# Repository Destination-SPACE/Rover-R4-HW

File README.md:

# Destination Automation R4 - Hardware test
Hardware repository for the Destination Automation R4 robotic rover platform

## Features
- Seeeduino XIAO SAMD21 M0 microcontroller
- +5V & +8V voltage regulators
- 128x64 OLED display
- 2x DRV8871 full bridge motor drivers
- Line follwer connector (JST-PH)
- 2x input buttons

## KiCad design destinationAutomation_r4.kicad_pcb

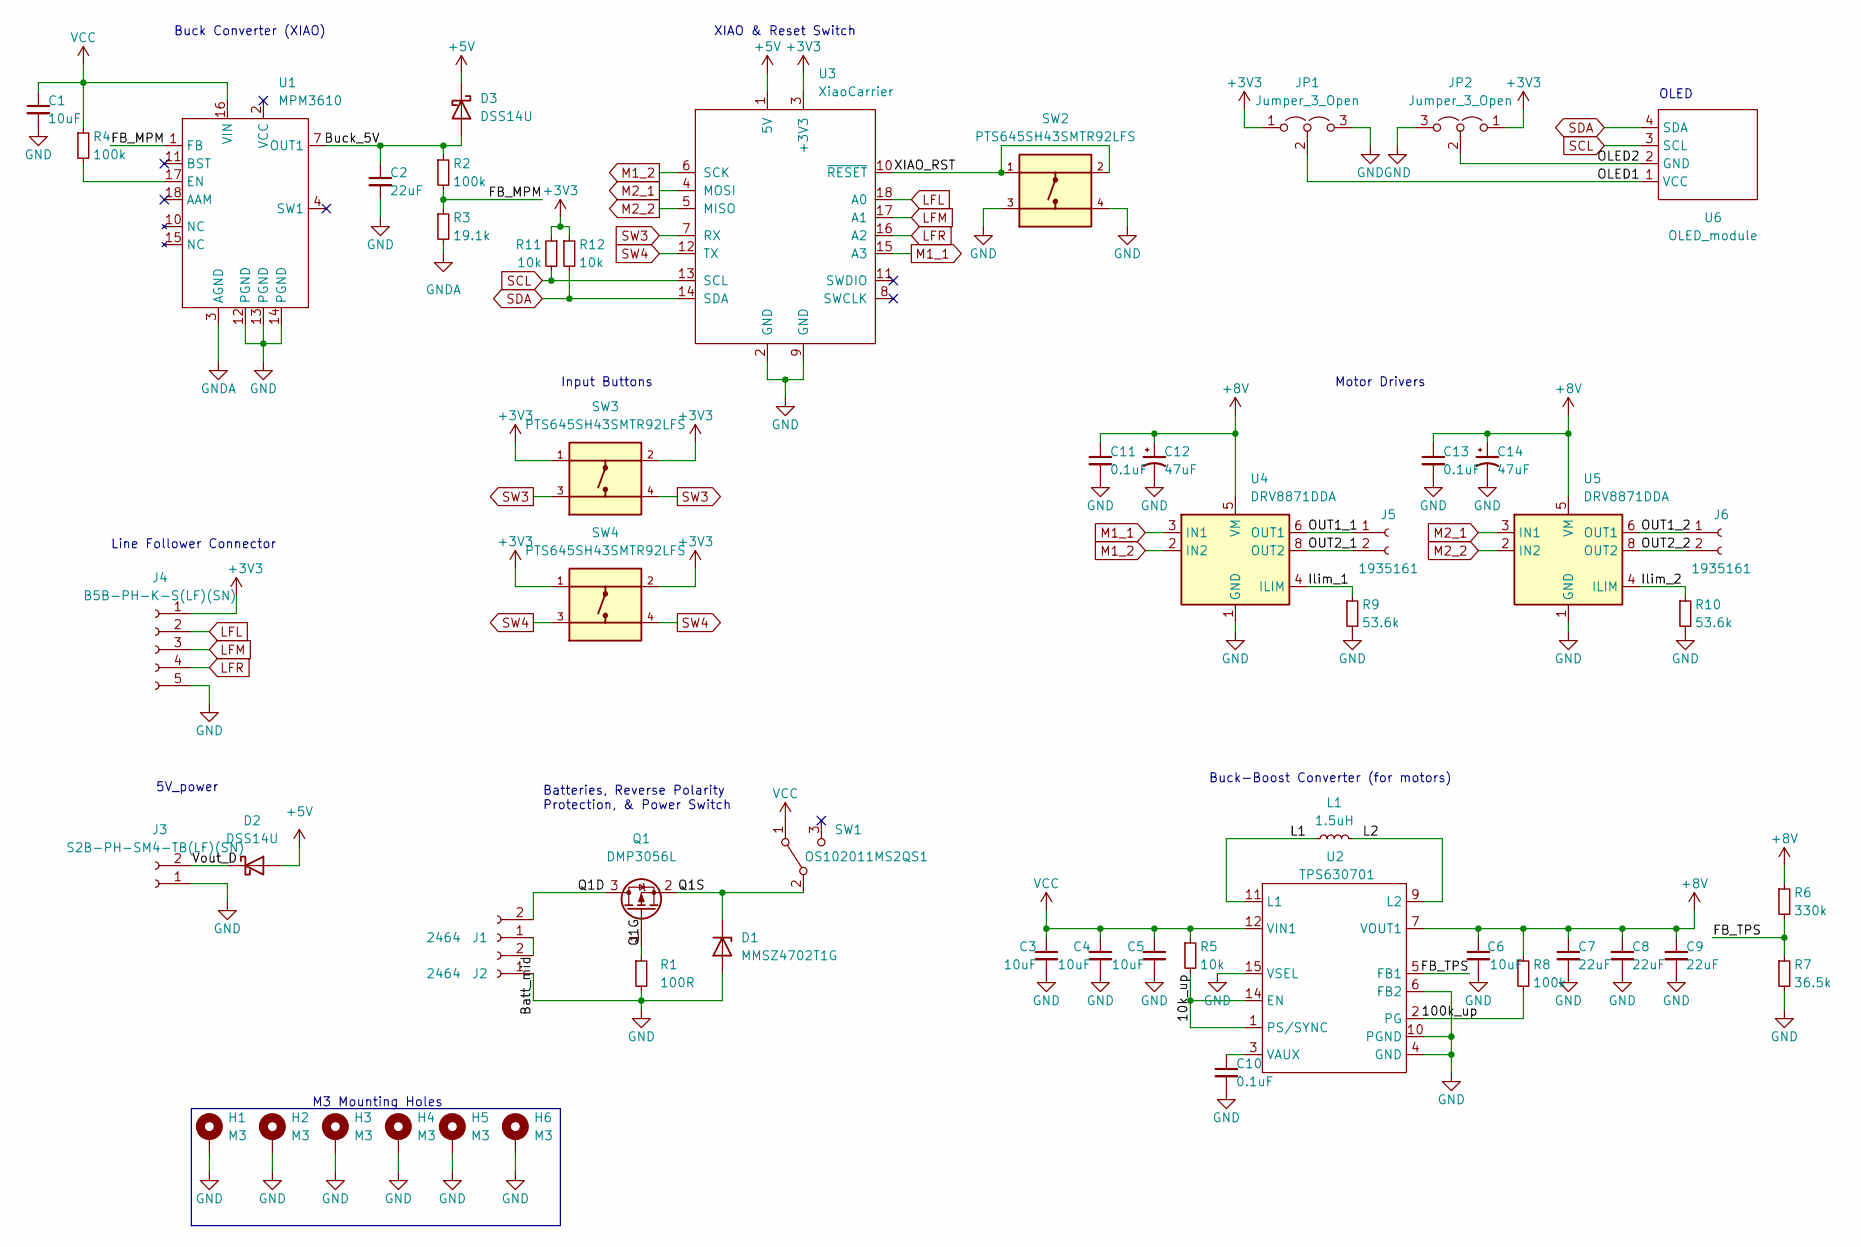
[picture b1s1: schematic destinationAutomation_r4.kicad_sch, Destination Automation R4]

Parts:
C1, C3, C4: 10uF; C_0805_2012Metric; mpn C2012X7R1A106K125AC
C2, C7, C8, C9: 22uF; C_0805_2012Metric; mpn C2012X5R1C226M125AC
C5, C6: 10uF; C_0603_1608Metric; mpn C1608X5R1C106M080AB
C10, C11, C13: 0.1uF; C_0603_1608Metric; mpn CGA3E2X7R1E104K080AA
C12, C14: 47uF; CP_Elec_6.3x7.7; mpn EDK476M035A9GAA
D1: MMSZ4702T1G; D_SOD-123; mpn MMSZ4702T1G
D2, D3: DSS14U; D_SOD-123F; mpn DSS14U
H1, H2, H3, H4, H5, H6: M3; MountingHole_3.2mm_M3_DIN965_Pad
J1, J2: 2464; 2464BatteryPack; mpn 2464
J3: S2B-PH-SM4-TB(LF)(SN); JST_PH_S2B-PH-SM4-TB_1x02-1MP_P2.00mm_Horizontal; mpn S2B-PH-SM4-TB(LF)(SN)
J4: B5B-PH-K-S(LF)(SN); JST_PH_B5B-PH-K_1x05_P2.00mm_Vertical; mpn B5B-PH-K-S(LF)(SN)
J5, J6: 1935161; SolderWire-1sqmm_1x02_P5.4mm_D1.4mm_OD2.7mm; mpn 1935161
JP1, JP2: Jumper_3_Open; SolderJumper-3_P1.3mm_Open_RoundedPad1.0x1.5mm
L1: 1.5uH; DRA74; mpn DR74-1R5-R
Q1: DMP3056L; SOT-23; mpn DMP3056L-7
R1: 100R; R_0603_1608Metric; mpn CRCW0603100RFKEA
R2, R4, R8: 100k; R_0603_1608Metric; mpn CRCW0603100KJNEA
R3: 19.1k; R_0603_1608Metric; mpn CRCW060319K1FKEA
R5, R11, R12: 10k; R_0603_1608Metric; mpn CRCW060310K0JNEB
R6: 330k; R_0603_1608Metric; mpn CRCW0603330KFKEAC
R7: 36.5k; R_0603_1608Metric; mpn CRCW060336K5FKEA
R9, R10: 53.6k; R_0603_1608Metric; mpn CRCW060353K6FKEAC
SW1: OS102011MS2QS1; SW_SPDT; mpn OS102011MS2QS1
SW2, SW3, SW4: PTS645SH43SMTR92LFS; MF_Switches-TACT6MM; mpn PTS645SH43SMTR92LFS
U1: MPM3610; mpn MPM3610GQV-P
U2: TPS630701; RNM0015A; mpn TPS63070RNMR
U3: XiaoCarrier; mpn 102010328
U4: DRV8871DDA; Texas_HTSOP-8-1EP_3.9x4.9mm_P1.27mm_EP2.95x4.9mm_Mask2.4x3.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; mpn DRV8871DDAR
U5: DRV8871DDA; Texas_HTSOP-8-1EP_3.9x4.9mm_P1.27mm_EP2.95x4.9mm_Mask2.4x3.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; mpn DRV8871DDA
U6: OLED_module

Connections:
+3V3: J4.1, JP1.1 (A), JP2.1 (A), R11.1, R12.1, SW3.1, SW3.2, SW4.1, SW4.2, U3.3 (+3V3)
+5V: D2.2 (A), D3.1 (K), U3.1 (5V)
+8V: C6.1, C7.1, C8.1, C9.1, C11.1, C12.1, C13.1, C14.1, R6.1, R8.1, U2.7 (VOUT1), U4.5 (VM), U5.5 (VM)
/10k_up: R5.2, U2.1 (PS/SYNC), U2.14 (EN)
/100k_up: R8.2, U2.2 (PG)
/Batt_mid: J1.1, J2.2
/Buck_5V: C2.1, D3.2 (A), R2.1, U1.7 (OUT1)
/FB_MPM: R2.2, R3.1, U1.1 (FB)
/FB_TPS: R6.2, R7.1, U2.5 (FB1)
/Ilim_1: R9.1, U4.4 (ILIM)
/Ilim_2: R10.1, U5.4 (ILIM)
/L1: L1.1, U2.11 (L1)
/L2: L1.2, U2.9 (L2)
/OLED1: JP1.2 (C), U6.1 (VCC)
/OLED2: JP2.2 (C), U6.2 (GND)
/OUT1_1: J5.1, U4.6 (OUT1)
/OUT1_2: J6.1, U5.6 (OUT1)
/OUT2_1: J5.2, U4.8 (OUT2)
/OUT2_2: J6.2, U5.8 (OUT2)
/Q1D: J1.2, Q1.3 (D)
/Q1G: Q1.1 (G), R1.1
/Q1S: D1.1 (K), Q1.2 (S), SW1.2 (B)
/Vout_D: D2.1 (K), J3.2
/XIAO_RST: SW2.1, SW2.2, U3.10 (~RESET)
GND: C1.2, C2.2, C3.2, C4.2, C5.2, C6.2, C7.2, C8.2, C9.2, C10.2, C11.2, C12.2, C13.2, C14.2, D1.2 (A), H1.1, H2.1, H3.1, H4.1, H5.1, H6.1, J2.1, J3.1, J4.5, JP1.3 (B), JP2.3 (B), R1.2, R7.2, R9.2, R10.2, SW2.3, SW2.4, U1.12 (PGND), U1.13 (PGND), U1.14 (PGND), U2.4 (GND), U2.6 (FB2), U2.10 (PGND), U2.15 (VSEL), U3.2 (GND), U3.9 (GND), U4.1 (GND), U4.7 (GND), U4.9 (GND), U5.1 (GND), U5.7 (GND), U5.9 (GND)
GNDA: R3.2, U1.3 (AGND)
LFL: J4.2, U3.18 (A0)
LFM: J4.3, U3.17 (A1)
LFR: J4.4, U3.16 (A2)
M1_1: U3.15 (A3), U4.3 (IN1)
M1_2: U3.6 (SCK), U4.2 (IN2)
M2_1: U3.4 (MOSI), U5.3 (IN1)
M2_2: U3.5 (MISO), U5.2 (IN2)
unnamed: C10.1, U2.3 (VAUX)
unnamed: R4.2, U1.17 (EN)
SCL: R11.2, U3.13 (SCL), U6.3 (SCL)
SDA: R12.2, U3.14 (SDA), U6.4 (SDA)
SW3: SW3.3, SW3.4, U3.7 (RX)
SW4: SW4.3, SW4.4, U3.12 (TX)
VCC: C1.1, C3.1, C4.1, C5.1, R4.1, R5.1, SW1.1 (A), U1.16 (VIN), U2.12 (VIN1)

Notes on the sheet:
Buck-Boost Converter (for motors)
Input Buttons
XIAO & Reset Switch
Buck Converter (XIAO)
5V_power
M3 Mounting Holes
Line Follower Connector
OLED
Motor Drivers
Batteries, Reverse Polarity Protection, & Power Switch

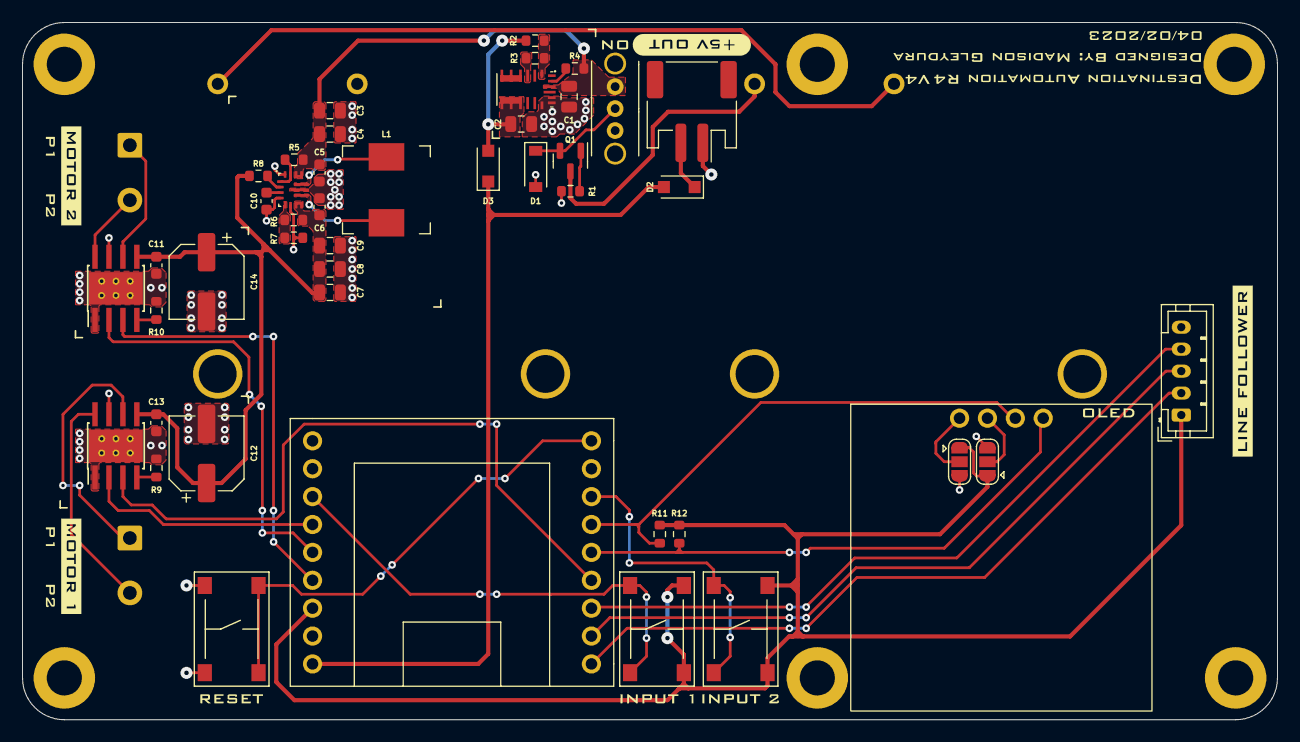
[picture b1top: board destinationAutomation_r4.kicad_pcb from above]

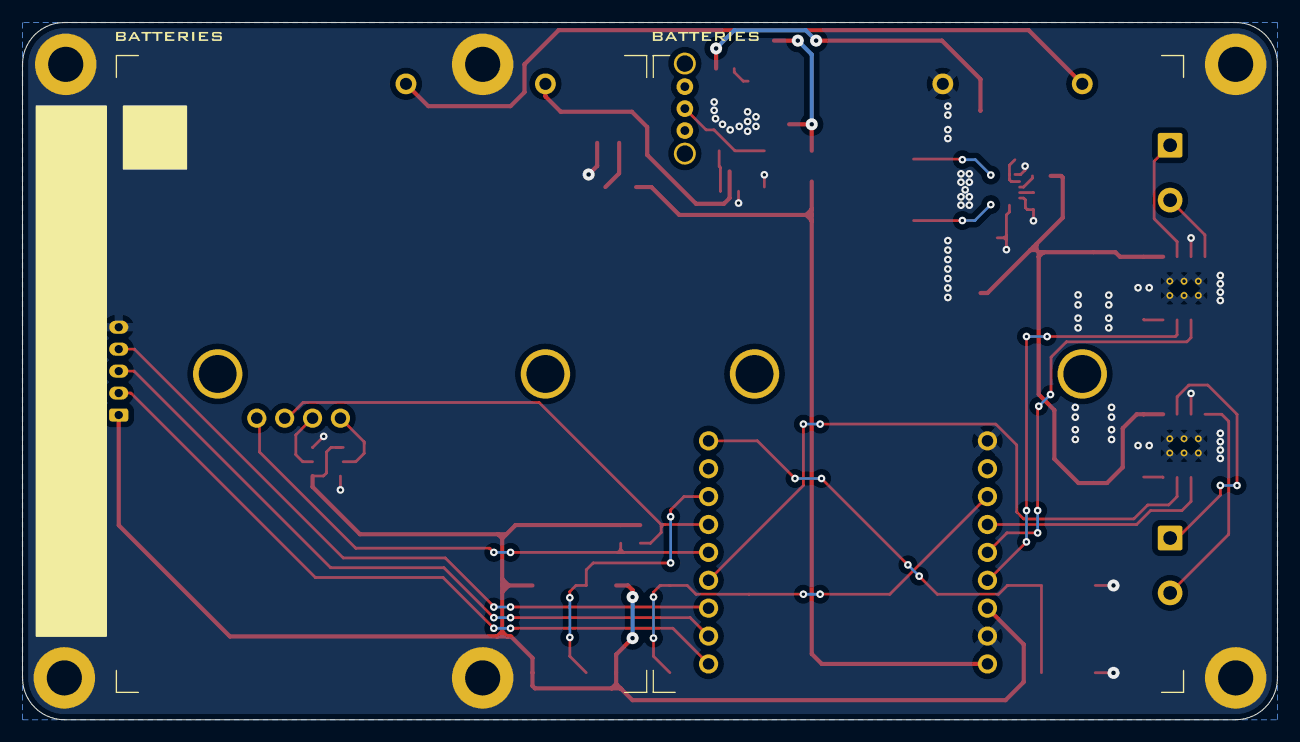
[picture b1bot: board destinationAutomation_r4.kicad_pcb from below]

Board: 2 copper layers, 114.3 x 63.5 mm, 72 parts (4 on the bottom side), 40 nets.

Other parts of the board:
kibuzzard-63BADBE9: G***; kibuzzard-63BADBE9
kibuzzard-63BADD9E: G***; kibuzzard-63BADD9E
kibuzzard-63BADE14: G***; kibuzzard-63BADE14
kibuzzard-63BADEE3: G***; kibuzzard-63BADEE3
kibuzzard-63BAE25F, kibuzzard-63BAE25F#2: G***; kibuzzard-63BAE25F
kibuzzard-63BAE271, kibuzzard-63BAE271#2: G***; kibuzzard-63BAE271
kibuzzard-63BAECD9: G***; kibuzzard-63BAECD9
kibuzzard-63BAECE0: G***; kibuzzard-63BAECE0
kibuzzard-63BAECF6: G***; kibuzzard-63BAECF6
kibuzzard-63BAED05: G***; kibuzzard-63BAED05
kibuzzard-63BAED20: G***; kibuzzard-63BAED20
kibuzzard-63BAED92, kibuzzard-63BAED92#2: G***; kibuzzard-63BAED92
kibuzzard-6429DDBF: G***; kibuzzard-6429DDBF
kibuzzard-6429DDCA: G***; kibuzzard-6429DDCA

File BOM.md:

| Item | Qty | Reference(s)   | Value                 | Manufacturer                  | mpn                   |
| ---- | --- | -------------- | --------------------- | ----------------------------- | --------------------- |
| 1    | 3   | C1, C3, C4     | 10uF                  | TDK Corporation               | C2012X7R1A106K125AC   |
| 2    | 4   | C2, C7, C8, C9 | 22uF                  | TDK Corporation               | C2012X5R1C226M125AC   |
| 3    | 2   | C5, C6         | 10uF                  | TDK Corporation               | C1608X5R1C106M080AB   |
| 4    | 3   | C10, C11, C13  | 0.1uF                 | TDK Corporation               | CGA3E2X7R1E104K080AA  |
| 5    | 2   | C12, C14       | 47uF                  | Kemet                         | EDK476M035A9GAA       |
| 6    | 1   | D1             | MMSZ4702T1G           | Onsemi                        | MMSZ4702T1G           |
| 7    | 2   | D2, D3         | DSS14U                | SMC Diode Solutions           | DSS14U                |
| 9    | 2   | J1, J2         | 2464                  | Keystone Electronics          | 2464                  |
| 10   | 1   | J3             | S2B-PH-SM4-TB(LF)(SN) | JST Sales America Inc.        | S2B-PH-SM4-TB(LF)(SN) |
| 11   | 1   | J4             | B5B-PH-K-S(LF)(SN)    | JST Sales America Inc.        | B5B-PH-K-S(LF)(SN)    |
| 12   | 2   | J5, J6         | 1935161               | Phoenix Contact               | 1935161               |
| 15   | 1   | L1             | 1.5uH                 | Eaton - Electronics Division  | DR74-1R5-R            |
| 16   | 1   | Q1             | DMP3056L              | Diodes Incorporated           | DMP3056L-7            |
| 17   | 1   | R1             | 100R                  | Vishay Dale                   | CRCW0603100RFKEA      |
| 18   | 3   | R2, R4, R8     | 100k                  | Vishay Dale                   | CRCW0603100KJNEA      |
| 19   | 1   | R3             | 19.1k                 | Vishay Dale                   | CRCW060319K1FKEA      |
| 20   | 3   | R5, R11, R12   | 10k                   | Vishay Dale                   | CRCW060310K0JNEB      |
| 21   | 1   | R6             | 330k                  | Vishay Dale                   | CRCW0603330KFKEAC     |
| 22   | 1   | R7             | 36.5k                 | Vishay Dale                   | CRCW060336K5FKEA      |
| 23   | 2   | R9, R10        | 53.6k                 | Vishay Dale                   | CRCW060353K6FKEAC     |
| 24   | 1   | SW1            | OS102011MS2QS1        | C&K                           | OS102011MS2QS1        |
| 25   | 3   | SW2, SW3, SW4  | PTS645SH43SMTR92LFS   | C&K                           | PTS645SH43SMTR92LFS   |
| 26   | 1   | U1             | MPM3610               | Monolithic Power Systems Inc. | MPM3610GQV-P          |
| 27   | 1   | U2             | TPS630701             | Texas Instruments             | TPS63070RNMR          |
| 28   | 1   | U3             | XiaoCarrier           | Seeed Technology Co., Ltd     | 102010328             |
| 29   | 2   | U4, U5         | DRV8871DDA            | Texas Instruments             | DRV8871DDAR           |
| 30   | 1   | U6             | OLED module           | Frienda                       | B08VNNCLHD            |

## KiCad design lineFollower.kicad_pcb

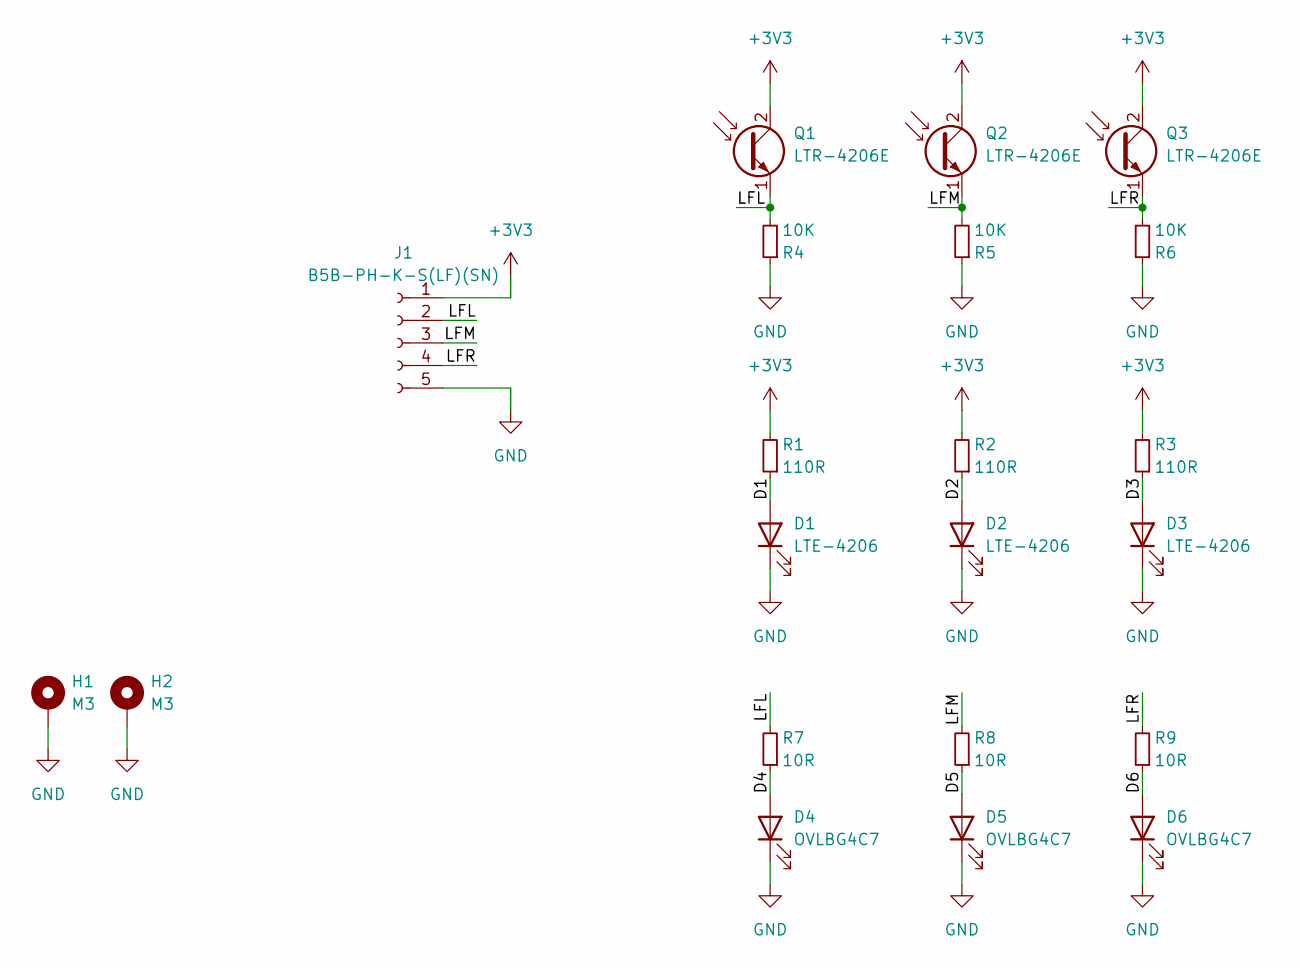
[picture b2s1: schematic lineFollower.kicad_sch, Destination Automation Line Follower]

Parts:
D1, D2, D3: LTE-4206; LED_D3.0mm; mpn LTE-4206
D4, D5, D6: OVLBG4C7; LED_D3.0mm; mpn OVLBG4C7
H1, H2: M3; MountingHole_3.2mm_M3_DIN965_Pad
J1: B5B-PH-K-S(LF)(SN); JST_PH_B5B-PH-K_1x05_P2.00mm_Vertical; mpn B5B-PH-K-S(LF)(SN)
Q1, Q2, Q3: LTR-4206E; LED_D3.0mm; mpn LTR-4206E
R1, R2, R3: 110R; R_Axial_DIN0207_L6.3mm_D2.5mm_P10.16mm_Horizontal; mpn CF14JT110R
R4, R5, R6: 10K; R_Axial_DIN0207_L6.3mm_D2.5mm_P10.16mm_Horizontal; mpn CF14JT10K0
R7, R8, R9: 10R; R_Axial_DIN0207_L6.3mm_D2.5mm_P10.16mm_Horizontal; mpn CF14JT10R0

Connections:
+3V3: J1.1, Q1.2 (C), Q2.2 (C), Q3.2 (C), R1.2, R2.2, R3.2
/D1: D1.1 (A), R1.1
/D2: D2.1 (A), R2.1
/D3: D3.1 (A), R3.1
/D4: D4.1 (A), R7.1
/D5: D5.1 (A), R8.1
/D6: D6.1 (A), R9.1
/LFL: J1.2, Q1.1 (E), R4.2, R7.2
/LFM: J1.3, Q2.1 (E), R5.2, R8.2
/LFR: J1.4, Q3.1 (E), R6.2, R9.2
GND: D1.2 (K), D2.2 (K), D3.2 (K), D4.2 (K), D5.2 (K), D6.2 (K), H1.1, H2.1, J1.5, R4.1, R5.1, R6.1

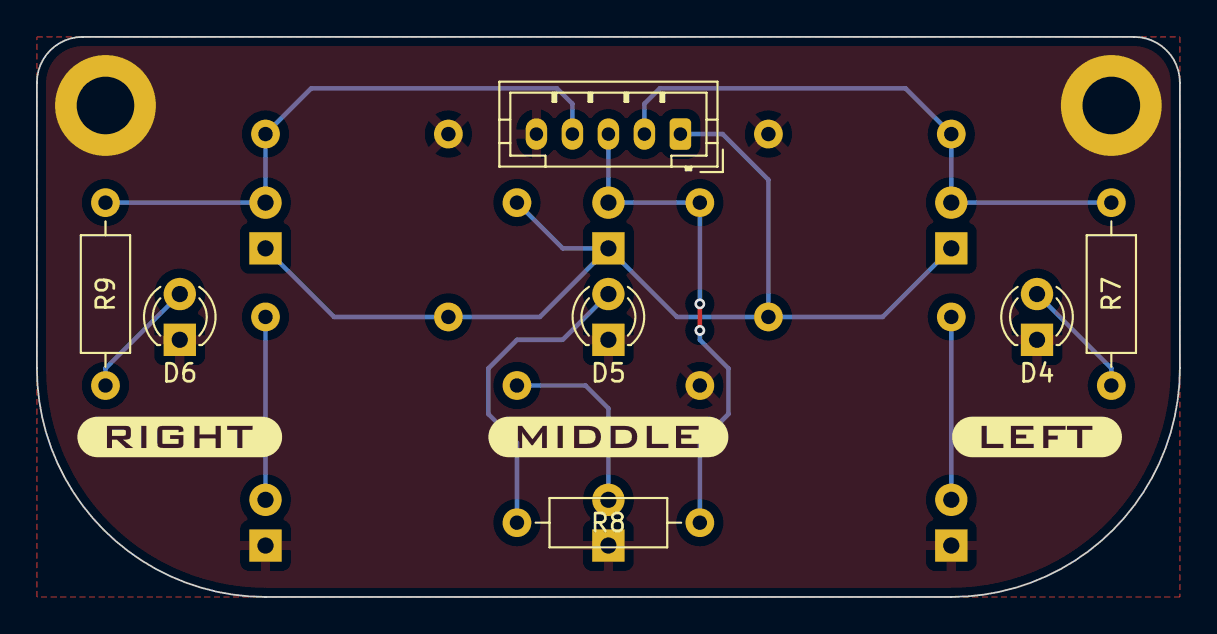
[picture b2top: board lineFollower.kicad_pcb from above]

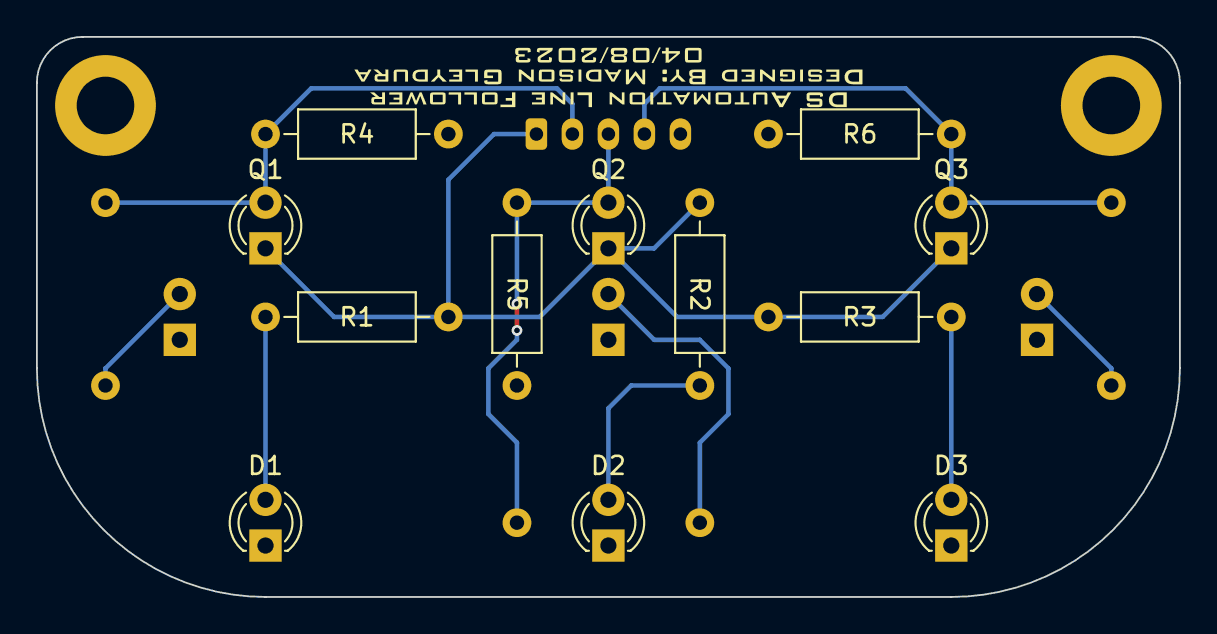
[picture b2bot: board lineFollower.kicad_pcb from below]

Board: 2 copper layers, 63.5 x 31.1 mm, 27 parts (15 on the bottom side), 11 nets.

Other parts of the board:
kibuzzard-63C6EA3C: G***; kibuzzard-63C6EA3C
kibuzzard-63C6EA52: G***; kibuzzard-63C6EA52
kibuzzard-63C70C4D: G***; kibuzzard-63C70C4D
kibuzzard-63C70C5D: G***; kibuzzard-63C70C5D
kibuzzard-63C70C70: G***; kibuzzard-63C70C70
kibuzzard-64320428: G***; kibuzzard-64320428

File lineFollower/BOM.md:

| Item | Qty | Reference(s) | Value              | Manufacturer                    | mpn                |
| ---- | --- | ------------ | ------------------ | ------------------------------- | ------------------ |
| 1    | 3   | D1, D2, D3   | LTE-4206           | Lite-On Inc.                    | LTE-4206           |
| 2    | 3   | D4, D5, D6   | OVLBG4C7           | TT Electronics/Optek Technology | OVLBG4C7           |
| 4    | 1   | J1           | B5B-PH-K-S(LF)(SN) | JST Sales America Inc.          | B5B-PH-K-S(LF)(SN) |
| 5    | 3   | Q1, Q2, Q3   | LTR-4206E          | Lite-On Inc.                    | LTR-4206E          |
| 6    | 3   | R1, R2, R3   | 110R               | Stackpole Electronics Inc       | CF14JT110R         |
| 7    | 3   | R4, R5, R6   | 10K                | Stackpole Electronics Inc       | CF14JT10K0         |
| 8    | 3   | R7, R8, R9   | 10R                | Stackpole Electronics Inc       | CF14JT10R0         |

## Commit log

2023-04-09 Create LICENSE
2023-04-09 test
